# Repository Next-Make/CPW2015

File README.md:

# CPW2015
AVR code for CPW 2015 soldering event.

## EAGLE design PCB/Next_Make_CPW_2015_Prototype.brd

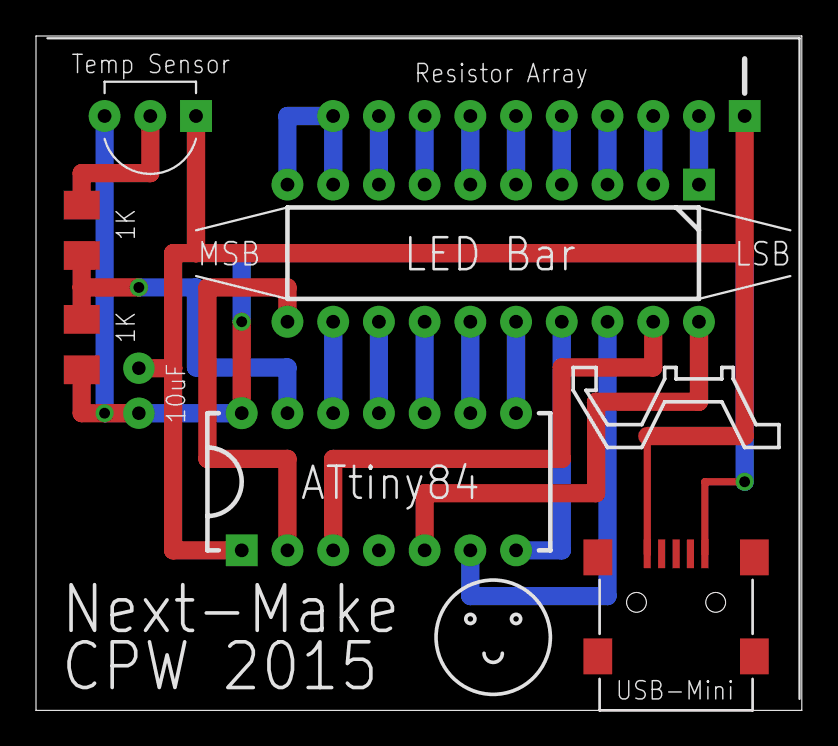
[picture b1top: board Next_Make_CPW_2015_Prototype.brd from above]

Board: 2 copper layers, 42.5 x 37.5 mm, 8 parts (0 on the bottom side), 23 nets.

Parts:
R1, R2: 1K; M1206
U$1: 9X_1K_BUSSED_R; SIP-10
U$2: 10UF_FK18; CAP_FK18
U$3: ATTINY84A; PDIP-14
U$4: LED_X10_BAR
U$5: MCP9701; TO-92-3
U$6: USB_MINI; SMT_MINI_USB

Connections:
5V: U$1.PIN_1, U$2.PIN_2, U$3.PIN_1, U$5.PIN_1, U$6.+5V
GND: R1.2, U$2.PIN_1, U$3.PIN_14, U$5.PIN_3, U$6.GND
unnamed: U$1.PIN_2, U$4.PIN_1
unnamed: U$1.PIN_3, U$4.PIN_2
unnamed: U$1.PIN_4, U$4.PIN_3
unnamed: U$1.PIN_5, U$4.PIN_4
unnamed: U$1.PIN_6, U$4.PIN_5
unnamed: U$1.PIN_7, U$4.PIN_6
unnamed: U$1.PIN_8, U$4.PIN_7
unnamed: U$1.PIN_9, U$4.PIN_8
unnamed: R2.1, U$5.PIN_2
unnamed: R1.1, R2.2, U$3.PIN_13
unnamed: U$3.PIN_11, U$4.PIN_13
unnamed: U$3.PIN_12, U$4.PIN_12
unnamed: U$3.PIN_10, U$4.PIN_14
unnamed: U$3.PIN_9, U$4.PIN_15
unnamed: U$3.PIN_8, U$4.PIN_16
unnamed: U$3.PIN_7, U$4.PIN_17
unnamed: U$3.PIN_6, U$4.PIN_18
unnamed: U$3.PIN_3, U$4.PIN_19
unnamed: U$3.PIN_5, U$4.PIN_20
unnamed: U$1.PIN_10, U$4.PIN_9, U$4.PIN_10
unnamed: U$3.PIN_2, U$4.PIN_11

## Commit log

2015-01-18 cleanup
2015-02-21 added BOM and folder
2015-02-21 added blank C code file
2015-02-21 added blank lbr file
2015-02-21 Added mini-usb connector to eagle library
2015-02-21 library updated with all parts
2015-02-21 Finished library, added schematic, added pcb
2015-02-21 removed backup files
2015-02-22 proto board complete
2015-02-22 changed file names
2015-03-04 removed empty file and added preliminary code
2015-03-08 Added some haikus for the CPW boards
2015-03-15 Added google doc entries
2015-03-15 More haikus more haikus more haikus
2015-03-15 Cleaned up spacing, culled some haikus
2015-03-15 Plus more haikus
2015-03-15 Cleaned up apostrophes, standardized line numbers
2015-03-15 When will we ever stop
2015-03-15 More haikus more haikus more haikus more haikus etc etc
2015-03-15 final board design and updated library
2015-03-15 Update haikus.txt
    To misspell "MacGregor" is an eGREGious error.
2015-03-15 Tall Greg's Initial Commit - Four NEW Haikus
    Can you NAME that haiku? ;p
2015-03-15 Tall Greg's Initial Commit - Let's try that again
    Apparently I have counting issues
2015-03-15 After many trials and tribulations, we have narrowed down our haiku selection to the finest variety. We hope you enjoy them and have a nice day.
2015-03-15 Minor grammar fixes
    I sure hope my grammar is better than my counting an hour ago
2015-03-20 These are some haikus / We're now in the final stretch / Hope you enjoy them
2015-03-24 100 haikus / Finally we're ready to / Unleash on the world
2015-03-30 changed placeholder text to make script replacement easier
2015-03-31 updated board design with instuctions and resistive divider
2015-03-31 panelized boards and updated main brd file
2015-04-01 added gerber zips for panelized boards
2015-04-01 moved panelized brd files to their own folder
2015-04-01 moved gerber zips to panelized folder for organization
2015-04-07 updated panelized boards
2015-04-07 removed old panelized boards
2015-04-07 removed hidden junk file
2015-04-07 added schematic pdf, added final panelized boards, added final gerbers
2015-04-07 removed junk file
2015-04-07 removed old AVR Studio files
2015-04-07 remove avr studio files
2015-04-07 added C code and hex files
2015-04-12 added non-voted upon constitution
2015-04-12 added edited haiku list
2015-04-12 removed old hex files and update C code
2015-04-16 changed to refect final design
2015-04-16 rename
2015-04-16 renamed and added panelized brd pdf
2015-05-11 added avrdude terminal progamming command
2015-05-11 added CPW 2015 hex file
2016-03-29 Year-old errata / Should've counted syllables / Before my git push
